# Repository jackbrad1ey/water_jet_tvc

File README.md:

Storage and collaboration repository for MEC2402 water jet TVC development.
The purpose of this project was to design and construct a vehicle capable of testing TVC control algorithms. Water is used as its method of propulsion to greatly reduce costs and time during development and ensure safety, allowing for rapid iteration and testing of new control algorithms.

The project features:
- Neptune, a custom flight computer designed to handle communication with ground station, control our servo motors, read from sensors and more.
- Neptune's firmware, consisting of a real time operating system that reads from our sensors and executes instructions based on packets sent from ground station.
- Ground station software, which is used to interact with the vehicle via a Jumper T-lite controller.
- CAD files for the vehicle and the associated testing stand.

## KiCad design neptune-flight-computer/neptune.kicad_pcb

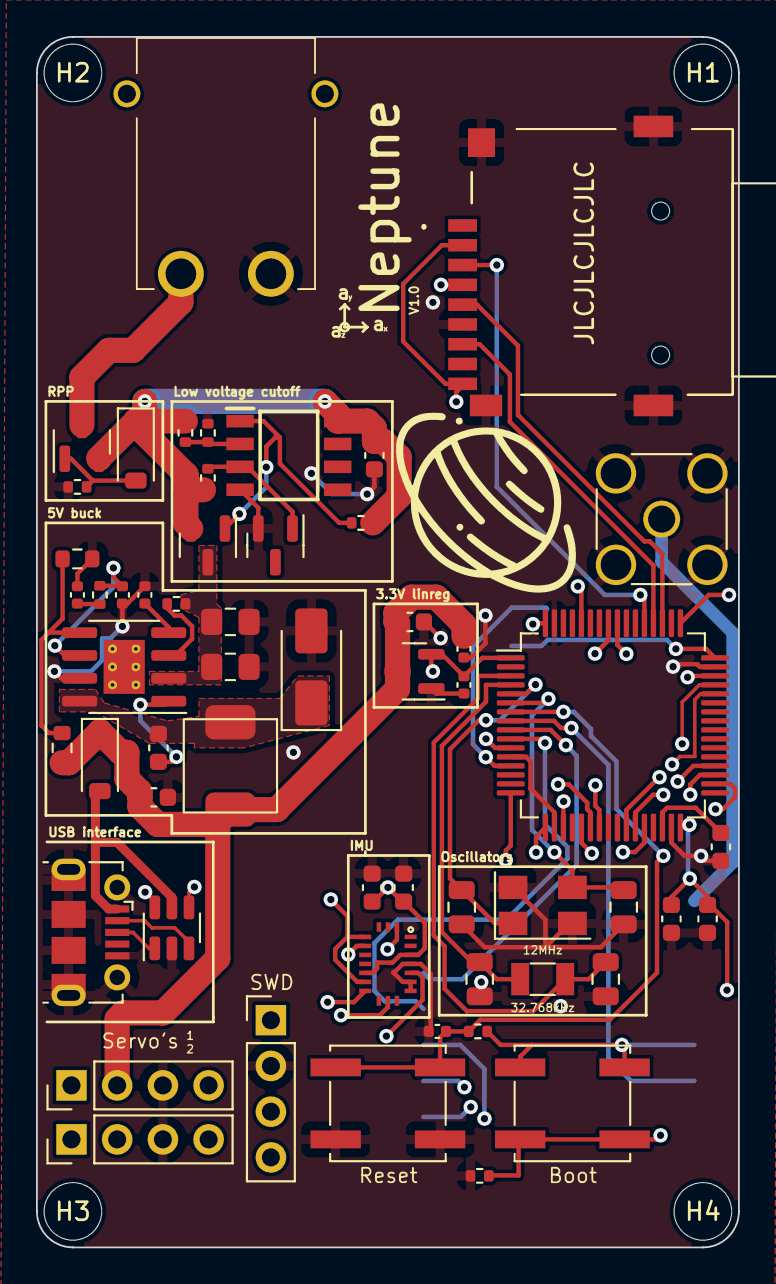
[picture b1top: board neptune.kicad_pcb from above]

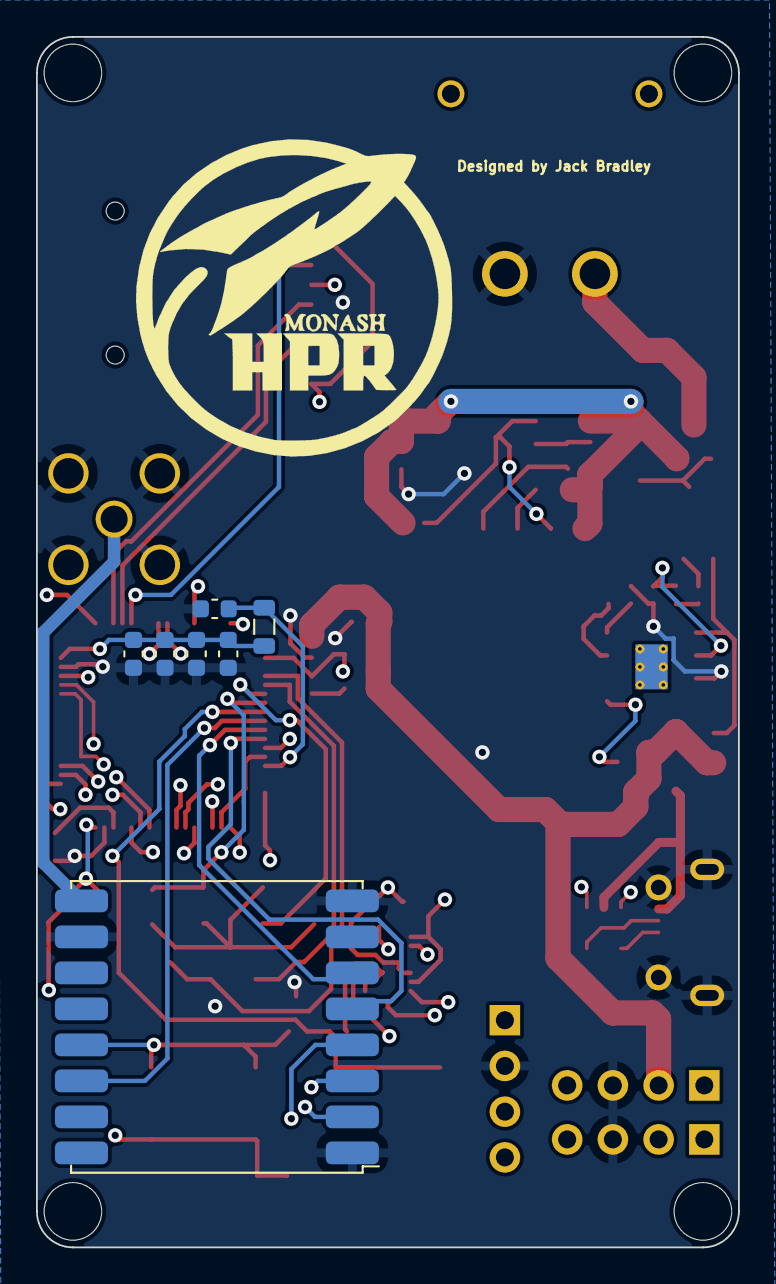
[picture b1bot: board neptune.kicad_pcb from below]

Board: 4 copper layers, 39.0 x 67.2 mm, 68 parts (8 on the bottom side), 54 nets.

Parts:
C1, C2: 15p; C_0805_2012Metric
C3, C21: 33p; C_0805_2012Metric
C4, C5, C6, C7, C8, C9, C10, C11, C24, C25: 100nF; C_0603_1608Metric
C12, C14: 10u; C_0805_2012Metric_Pad1.18x1.45mm_HandSolder
C13, C16, C20: 1u; C_0402_1005Metric
C15: 8.2n; C_0402_1005Metric
C17: 1n; C_0402_1005Metric
C18: 10p; C_0402_1005Metric
C19: 10u; C_0603_1608Metric
C22: 10n; C_0603_1608Metric
C23: 1u; C_0603_1608Metric
C26: 4.7u; C_0603_1608Metric
D1, D3: B5819W; D_SOD-123
D2: RB056LAM-40TR; D_SMA
H1, H2, H3, H4: MountingHole; MountingHole_3.2mm_M3
H5: HPR_Logo
J1: THD2528-11SD-GF; THD252811SDGF
J2: Conn_01x02; XT30PWM
J3: Conn_Coaxial; SMA_Amphenol_132291_Vertical
J4: USB_B_Micro; USB_Micro-B_Molex-105017-0001
J5, J6, J7: Conn_01x04; PinHeader_1x04_P2.54mm_Vertical
L1: IHLP2020CZER100M01
L2: 10u; L_0805_2012Metric
Q1: Si2301-TP; SOT-23
Q2: AO3401A; SOT-23
R1, R4: 30k; R_0402_1005Metric
R2, R5: 100k; R_0402_1005Metric
R3: 56k; R_0402_1005Metric
R6: NC; R_0402_1005Metric
R7: 36.5k; R_0402_1005Metric
R8: 10.2k; R_0603_1608Metric
R9: 1.91k; R_0603_1608Metric
R10, R11: 10k; R_0402_1005Metric
SW1, SW2: TS-1187A-B-A-B; SW_Push_1P1T_NO_CK_KSC6xxJ
U1: ADR5040ARTZ-2.048; SOT-23
U2: LM393; SOIC127P600X175-8N
U3: TPS54331D; SOIC-8-1EP_3.9x4.9mm_P1.27mm_EP2.29x3mm_ThermalVias
U4: LP3993-33B3F; SOT-23
U5: RFM95W-915S2; HOPERF_RFM9XW_SMD
U6: USBLC6-2SC6; SOT-23-6
U7: STM32F411RETx; LQFP-64_10x10mm_P0.5mm
U8: BMX055
Y1: 32.768k; Crystal_SMD_3215-2Pin_3.2x1.5mm
Y2: 12MHz; Crystal_SMD_5032-4Pin_5.0x3.2mm

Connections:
+3.3V: C4.1, C5.1, C16.1, J1.4 (VDD), U4.2 (VOUT), U5.13 (3.3V)
+3V3: C9.1, C10.1, C22.1, C23.1, C24.1, C25.1, J5.1, L2.1, R11.2, SW1.2, U7.1 (VBAT), U7.19 (VDD), U7.32 (VDD), U7.48 (VDD), U7.64 (VDD), U8.3 (VDD), U8.13 (VDDIO)
+5V: C6.1, C13.1, C19.1, D3.1 (K), J6.2, J7.2, L1.2, R8.2, U4.3 (VIN)
/CE_ACC: U7.26 (PB0), U8.16 (CSB1)
/CE_GYR: U7.27 (PB1), U8.5 (CSB2)
/CE_MAG: U7.28 (PB2), U8.20 (CSB3)
/CLK_SD: J1.5 (CLX), U7.51 (PC10)
/CS_RF: U5.5 (NSS), U7.10 (PC2)
/CS_SD: J1.2 (CD/DAT3), J1.9 (CD), U7.11 (PC3)
/IMU_MISO: U7.22 (PA6), U8.12 (SDO2), U8.17 (SDO1)
/IMU_MOSI: U7.23 (PA7), U8.11 (SDX)
/IMU_SCK: U7.21 (PA5), U8.9 (SCX)
/MISO_RF: U5.2 (MISO), U7.35 (PB14)
/MISO_SD: J1.7 (DAT0), U7.52 (PC11)
/MOSI_RF: U5.3 (MOSI), U7.36 (PB15)
/MOSI_SD: J1.3 (CMD), U7.53 (PC12)
/RESET_RF: U5.6 (RESET), U7.9 (PC1)
/RF_1O0: U5.14 (DIO0), U7.8 (PC0)
/SCK_RF: U5.4 (SCK), U7.34 (PB13)
/STM32/BOOT0: R10.2, SW1.1, U7.60 (BOOT0)
/STM32/NRST: C20.1, R11.1, SW2.2, U7.7 (NRST)
/STM32/OSC32_IN: C1.1, U7.3 (PC14), Y1.1
/STM32/OSC32_OUT: C2.1, U7.4 (PC15), Y1.2
/STM32/OSC_IN: C21.1, U7.5 (PH0), Y2.1
/STM32/OSC_OUT: C3.1, U7.6 (PH1), Y2.3
/STM32/S1_control: J6.1, U7.56 (PB4)
/STM32/S1_feedback: J6.4, U7.16 (PA2)
/STM32/S2_control: J7.1, U7.57 (PB5)
/STM32/S2_feedback: J7.4, U7.17 (PA3)
/STM32/SWCLK: J5.4, U7.49 (PA14)
/STM32/SWDIO: J5.3, U7.46 (PA13)
/STM32/USB_D+: U6.6 (I/O1), U7.45 (PA12)
/STM32/USB_D-: U6.4 (I/O2), U7.44 (PA11)
/STM32/USB_conn_D+: J4.3 (D+), U6.1 (I/O1)
/STM32/USB_conn_D-: J4.2 (D-), U6.3 (I/O2)
GND: C1.2, C2.2, C3.2, C4.2, C5.2, C6.2, C7.2, C9.2, C10.2, C11.2, C12.2, C13.2, C14.2, C15.2, C16.2, C17.2, C18.2, C19.2, C20.2, C21.2, C22.2, C23.2, C24.2, C25.2, C26.2, D2.2 (A), J1.6 (VSS), J1.MP1, J1.MP2, J1.MP3, J1.MP4, J2.2, J3.2 (Ext), J4.5 (GND), J4.6 (Shield), J5.2, J6.3, J7.3, R2.1, R4.1, R9.1, R10.1, SW2.1, U1.2 (A), U2.4 (V-), U3.7 (GND), U4.1 (GND), U5.1 (GND), U5.8 (GND), U5.10 (GND), U6.2 (GND), U7.12 (VSSA), U7.18 (VSS), U7.31 (VSS), U7.47 (VSS), U7.63 (VSS), U8.4 (GNDA), U8.6 (GNDIO), U8.7 (PS), Y2.2, Y2.4
unnamed: C17.1, R7.1
unnamed: D1.2 (A), Q1.1 (G), R2.2
unnamed: C8.2, D2.1 (K), L1.1, U3.8 (PH)
unnamed: J2.1, Q1.3 (D)
unnamed: J3.1 (In), U5.9 (ANT)
unnamed: Q2.1 (G), R5.1, U2.1
unnamed: R1.1, U1.1 (K), U2.3 (+)
unnamed: R3.1, R4.2, U2.2 (-)
unnamed: C8.1, U3.1 (BOOT)
unnamed: C18.1, R7.2, U3.6 (COMP)
unnamed: R6.1, U3.3 (EN)
unnamed: C15.1, U3.4 (SS)
unnamed: R8.1, R9.2, U3.5 (VSENSE)
unnamed: C26.1, U7.30 (VCAP1)
unnamed: C11.1, L2.2, U7.13 (VDDA)
VBUS: D3.2 (A), J4.1 (VBUS), U6.5 (VBUS)
VCC: C12.1, C14.1, Q2.3 (D), R6.2, U3.2 (VIN)
VDC: C7.1, D1.1 (K), Q1.2 (S), Q2.2 (S), R1.2, R3.2, R5.2, U2.8 (V+)

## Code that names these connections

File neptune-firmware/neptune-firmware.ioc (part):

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Mcu.Name=STM32F411R(C-E)Tx
Mcu.Package=LQFP64
Mcu.UserName=STM32F411RETx
PA11.Mode=Device_Only
PA11.Signal=USB_OTG_FS_DM
PA12.Mode=Device_Only
PA12.Signal=USB_OTG_FS_DP
PA13.Mode=Serial_Wire
PA13.Signal=SYS_JTMS-SWDIO
PA14.Mode=Serial_Wire
PA14.Signal=SYS_JTCK-SWCLK
PA2.GPIOParameters=GPIO_Label
PA2.GPIO_Label=S1_FBK
PA2.Signal=ADCx_IN2
PA3.GPIOParameters=GPIO_Label
PA3.GPIO_Label=S2_FBK
PA3.Signal=ADCx_IN3
PA5.GPIOParameters=GPIO_Label
PA5.GPIO_Label=IMU_SCK
PA5.Mode=Full_Duplex_Master
PA5.Signal=SPI1_SCK
PA6.GPIOParameters=GPIO_Label
PA6.GPIO_Label=IMU_MISO
PA6.Mode=Full_Duplex_Master
PA6.Signal=SPI1_MISO
PA7.GPIOParameters=GPIO_Label
PA7.GPIO_Label=IMU_MOSI
PA7.Mode=Full_Duplex_Master
PA7.Signal=SPI1_MOSI
PB0.GPIOParameters=GPIO_Label
PB0.GPIO_Label=ACC_CE
PB0.Signal=GPIO_Output
PB1.GPIOParameters=GPIO_Label
PB1.GPIO_Label=GYR_CE
PB1.Signal=GPIO_Output
PB13.GPIOParameters=GPIO_Label
PB13.GPIO_Label=RF_SCK
PB13.Mode=Full_Duplex_Master
PB13.Signal=SPI2_SCK
PB14.GPIOParameters=GPIO_Label
PB14.GPIO_Label=RF_MISO
PB14.Mode=Full_Duplex_Master
PB14.Signal=SPI2_MISO
PB15.GPIOParameters=GPIO_Label
PB15.GPIO_Label=RF_MOSI
PB15.Mode=Full_Duplex_Master
PB15.Signal=SPI2_MOSI
PB2.GPIOParameters=GPIO_Label
PB2.GPIO_Label=MAG_CE
PB2.Signal=GPIO_Output
PB4.GPIOParameters=GPIO_Label
PB4.GPIO_Label=S1_CTRL
PB4.Signal=S_TIM3_CH1
PB5.GPIOParameters=GPIO_Label
PB5.GPIO_Label=S2_CTRL
PB5.Signal=S_TIM3_CH2
PC0.GPIOParameters=GPIO_Label
PC0.GPIO_Label=RF_10O
PC0.Signal=GPXTI0
PC1.GPIOParameters=GPIO_Label
PC1.GPIO_Label=RF_RESET
PC1.Signal=GPIO_Output
PC10.GPIOParameters=GPIO_Label
PC10.GPIO_Label=SD_SCK
PC10.Mode=Full_Duplex_Master
PC10.Signal=SPI3_SCK
PC11.GPIOParameters=GPIO_Label
PC11.GPIO_Label=SD_MISO
PC11.Mode=Full_Duplex_Master
PC11.Signal=SPI3_MISO
PC12.GPIOParameters=GPIO_Label
PC12.GPIO_Label=SD_MOSI
PC12.Mode=Full_Duplex_Master
PC12.Signal=SPI3_MOSI
PC14-OSC32_IN.Mode=LSE-External-Oscillator
PC14-OSC32_IN.Signal=RCC_OSC32_IN
PC15-OSC32_OUT.Mode=LSE-External-Oscillator
PC15-OSC32_OUT.Signal=RCC_OSC32_OUT
PC2.GPIOParameters=GPIO_Label
PC2.GPIO_Label=RF_CE
PC2.Signal=GPIO_Output
PC3.GPIOParameters=GPIO_Label
PC3.GPIO_Label=SD_CE
PC3.Signal=GPIO_Output
PH0\ -\ OSC_IN.Mode=HSE-External-Oscillator
PH0\ -\ OSC_IN.Signal=RCC_OSC_IN
PH1\ -\ OSC_OUT.Mode=HSE-External-Oscillator
PH1\ -\ OSC_OUT.Signal=RCC_OSC_OUT
RCC.HSE_VALUE=12000000
RCC.SYSCLKFreq_VALUE=96000000
RCC.SYSCLKSource=RCC_SYSCLKSOURCE_PLLCLK
board=custom

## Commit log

2023-03-22 Testing from darby's laptop
2023-04-22 Removed test file
2023-04-22 Added power regulation circuity
2023-04-23 Renamed to Neptune
2023-04-23 Continued work on board
2023-04-24 Added oscillator, setup sensor SPI
2023-04-24 Continued pcb work
2023-04-24 Schematic done I think
2023-04-25 PCB done, pending review
2023-04-26 Added mounting holes
2023-04-26 Created production files
2023-04-27 Headaches
2023-04-27 Generated BOM
2023-05-01 Final PCB changes
2023-05-01 Removed flight computer zip
2023-05-01 Setting up pinout and clock settings
2023-05-08 Finished STM32 setup
2023-05-09 Setting up firmware
2023-05-09 Made basic servo test code
2023-05-13 Worked on proper structure
2023-05-14 Working on sensor code
2023-05-14 stuff
2023-05-15 Roll and pitch calculations in progress
2023-05-16 Oh god help me
2023-05-16 yeah
2023-05-17 Sensor reading success
2023-05-17 Finally, sensor reading works
2023-05-17 Working on integrating FYP code
2023-05-18 motor testing code
2023-05-18 Ready for some RF testing I think
2023-05-18 Setting up initial code
2023-05-18 Ready for initial testing
2023-05-19 Ready for some initial testing
2023-05-20 Slight changes
2023-05-20 Slight changes to try debug issues
2023-05-20 Preparing to switch to polling setup
2023-05-20 Reading for testing with polling
2023-05-20 Preliminary working model ready to debug jitter issues
2023-05-20 Ground station updated
2023-05-20 Merging main
2023-05-21 Ready to test sensors
2023-05-21 Ground station updates
2023-05-21 Firmware updates
2023-05-21 Pretty much ready for final testing
2023-05-22 Testing done
2023-05-23 Fixed corrupt PCB file, updated schematic
2023-05-24 Added CAD files
2023-06-21 Rolled back flight computer to before corrupted
